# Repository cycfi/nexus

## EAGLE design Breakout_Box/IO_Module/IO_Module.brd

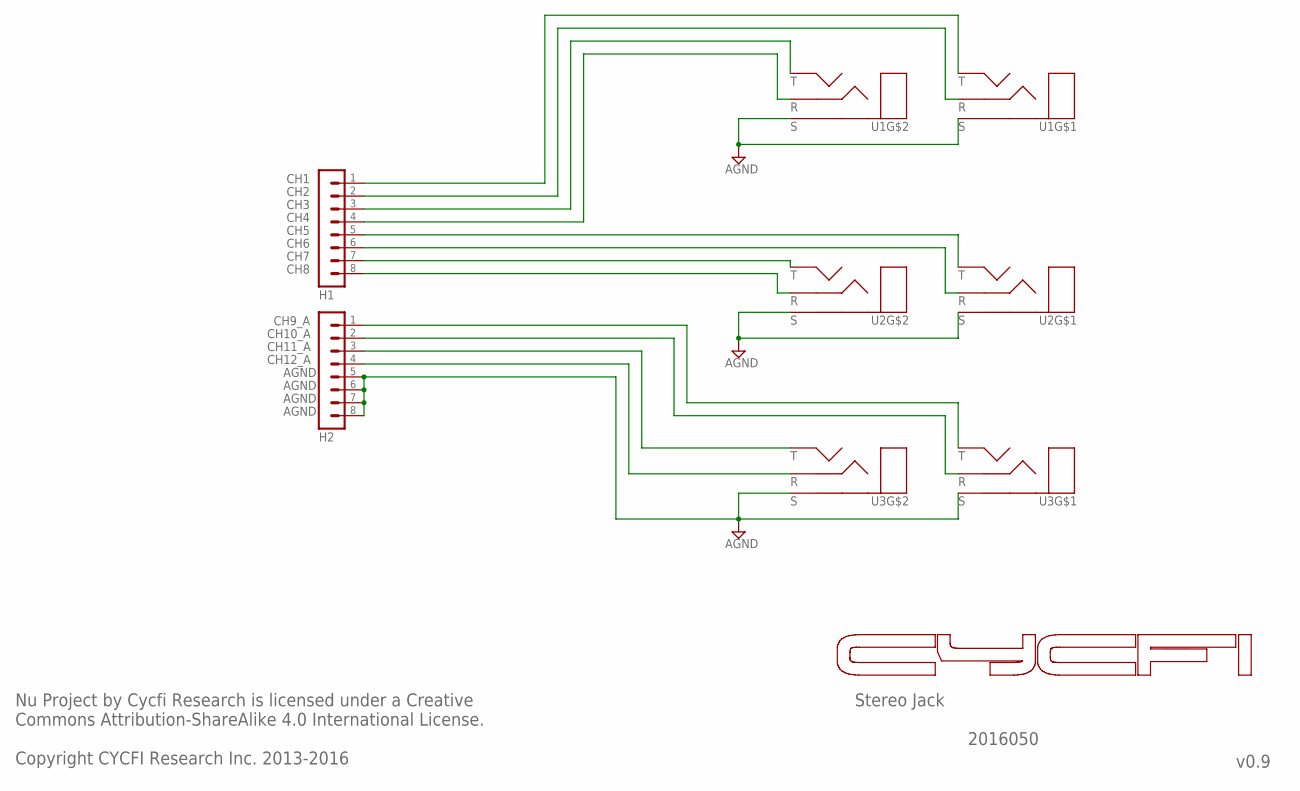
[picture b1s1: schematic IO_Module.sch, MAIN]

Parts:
H1, H2: MA08-1
U1, U2, U3: AGND; NSJ12HC

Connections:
AGND: H2.5, H2.6, H2.7, H2.8, U1.G (DGND), U1.SB (S), U1.ST (S), U2.G (DGND), U2.SB (S), U2.ST (S), U3.G (DGND), U3.SB (S), U3.ST (S)
unnamed: H1.1, U1.TT (T)
unnamed: H1.2, U1.RT (R)
unnamed: H1.3, U1.TB (T)
unnamed: H1.4, U1.RB (R)
unnamed: H1.5, U2.TT (T)
unnamed: H1.6, U2.RT (R)
unnamed: H1.7, U2.TB (T)
unnamed: H1.8, U2.RB (R)
unnamed: H2.1, U3.TT (T)
unnamed: H2.2, U3.RT (R)
unnamed: H2.3, U3.TB (T)
unnamed: H2.4, U3.RB (R)

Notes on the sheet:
Stereo Jack
v0.9
Nu Project by Cycfi Research is licensed under a Creative Commons Attribution-ShareAlike 4.0 International License. Copyright CYCFI Research Inc. 2013-2016
2016050
CH1
CH2
CH3
CH4
CH5
CH6
CH7
CH8
CH9_A
CH10_A
CH11_A
CH12_A

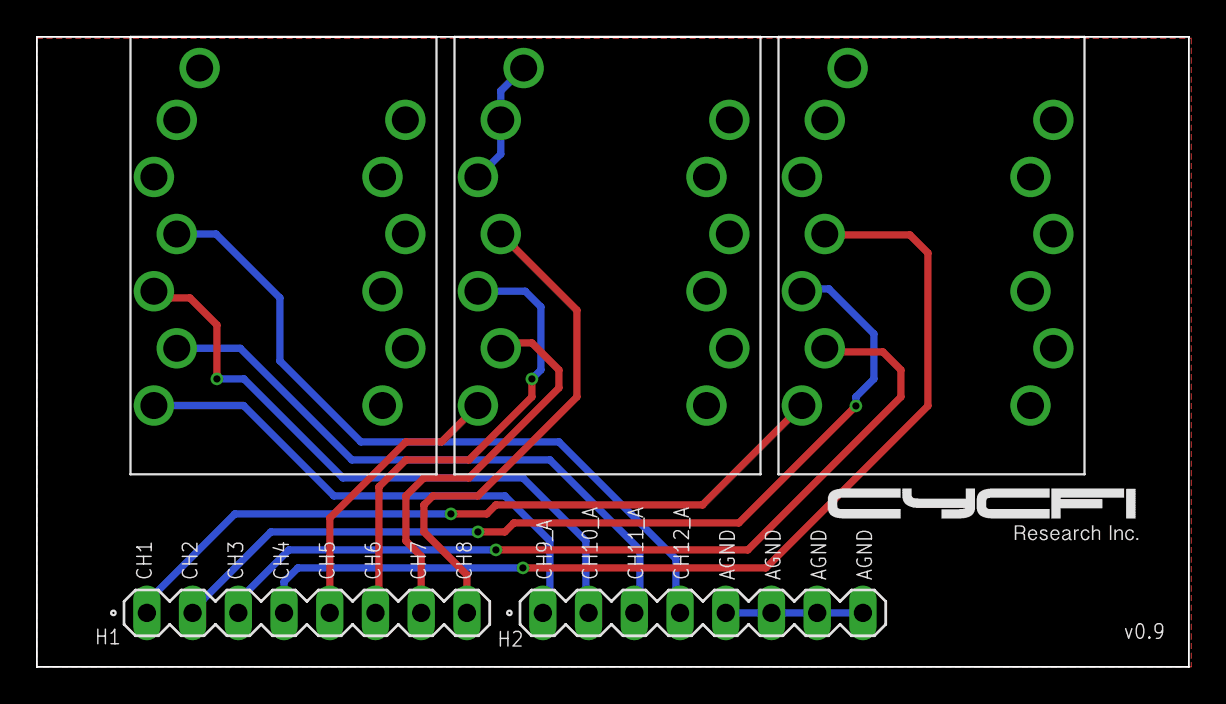
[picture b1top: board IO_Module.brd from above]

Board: 2 copper layers, 64.0 x 35.0 mm, 5 parts (0 on the bottom side), 13 nets.

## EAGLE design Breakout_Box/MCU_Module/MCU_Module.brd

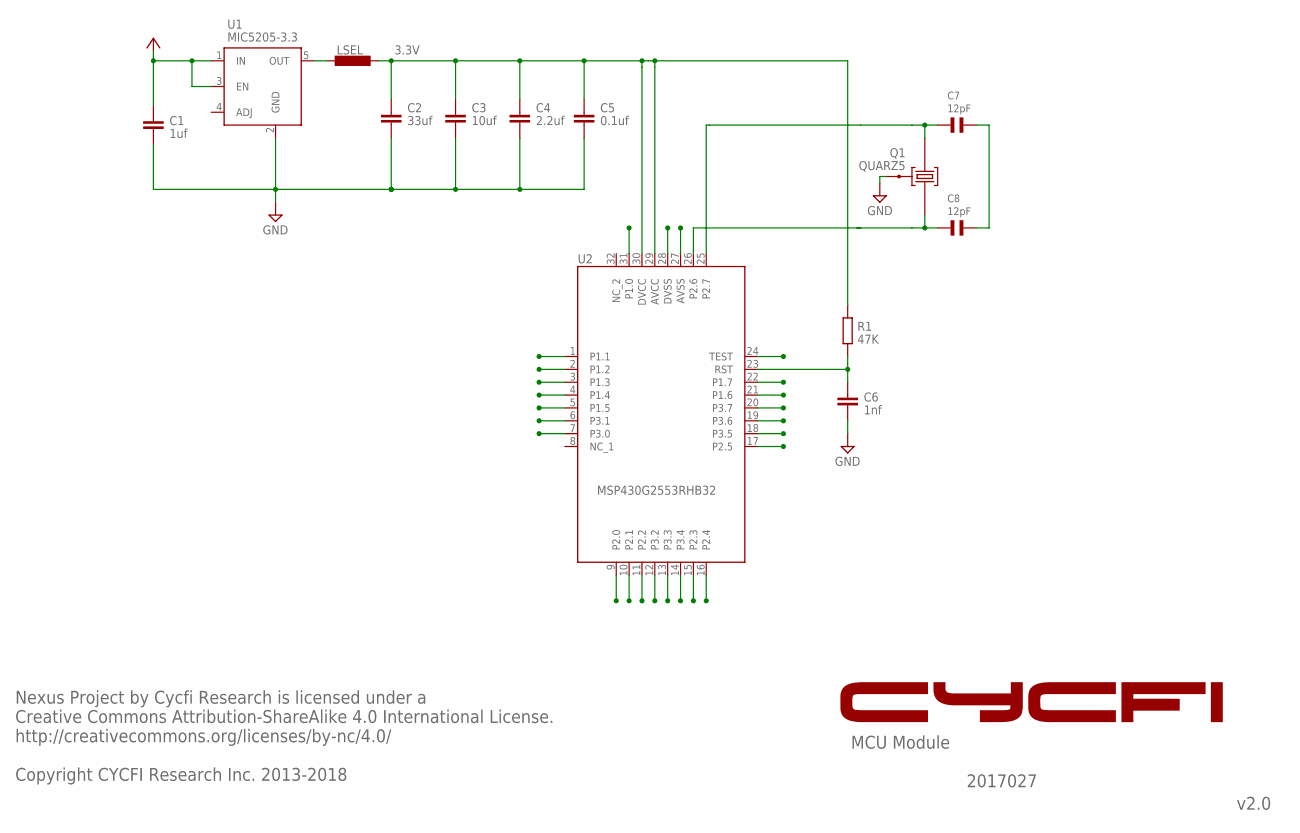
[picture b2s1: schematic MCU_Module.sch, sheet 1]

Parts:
C1: 1uf; C0805
C2: 33uf; C0805
C3: 10uf; C0805
C4: 2.2uf; C0805
C5: 0.1uf; C0603
C6: 1nf; C0603
C7, C8: 12pF; 0603
LSEL: FERRITE_BEAD; 0603
Q1: QUARZ5
R1: 47K; R0402
U1: MIC5205-3.3; SOT23-5
U2: MSP430G2553RHB32; QFN32

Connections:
!RST: C6.1, R1.2, U2.23 (RST); also elsewhere on the board
DVCC(3.3V): C2.1, C3.1, C4.1, C5.1, LSEL.2, R1.1, U2.29 (AVCC), U2.30 (DVCC); also elsewhere on the board
GND: C1.2, C2.2, C3.2, C4.2, C5.2, C6.2, C7.1, C8.1, Q1.GND@0 (0), U1.2 (GND), U2.27 (AVSS), U2.28 (DVSS); also elsewhere on the board
unnamed: LSEL.1, U1.5 (OUT)
NC_2: U2.32 (NC_2)
P1.0: U2.31 (P1.0); also elsewhere on the board
P1.1: U2.1 (P1.1); also elsewhere on the board
P1.2: U2.2 (P1.2); also elsewhere on the board
P1.3: U2.3 (P1.3); also elsewhere on the board
P1.4: U2.4 (P1.4); also elsewhere on the board
P1.5: U2.5 (P1.5); also elsewhere on the board
P1.6: U2.21 (P1.6); also elsewhere on the board
P1.7: U2.22 (P1.7); also elsewhere on the board
P2.0: U2.9 (P2.0); also elsewhere on the board
P2.1: U2.10 (P2.1); also elsewhere on the board
P2.2: U2.11 (P2.2); also elsewhere on the board
P2.3: U2.15 (P2.3); also elsewhere on the board
P2.4: U2.16 (P2.4); also elsewhere on the board
P2.5: U2.17 (P2.5); also elsewhere on the board
P2.6: C8.2, Q1.1, U2.26 (P2.6); also elsewhere on the board
P2.7: C7.2, Q1.2, U2.25 (P2.7); also elsewhere on the board
P3.0: U2.7 (P3.0); also elsewhere on the board
P3.1: U2.6 (P3.1); also elsewhere on the board
P3.2: U2.12 (P3.2); also elsewhere on the board
P3.3: U2.13 (P3.3); also elsewhere on the board
P3.4: U2.14 (P3.4); also elsewhere on the board
P3.5: U2.18 (P3.5); also elsewhere on the board
P3.6: U2.19 (P3.6); also elsewhere on the board
P3.7: U2.20 (P3.7); also elsewhere on the board
TEST: U2.24 (TEST); also elsewhere on the board
VCC: C1.1, U1.1 (IN), U1.3 (EN); also elsewhere on the board

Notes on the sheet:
3.3V
MCU Module
v2.0
Nexus Project by Cycfi Research is licensed under a Creative Commons Attribution-ShareAlike 4.0 International License. http://creativecommons.org/licenses/by-nc/4.0/ Copyright CYCFI Research Inc. 2013-2018
2017027

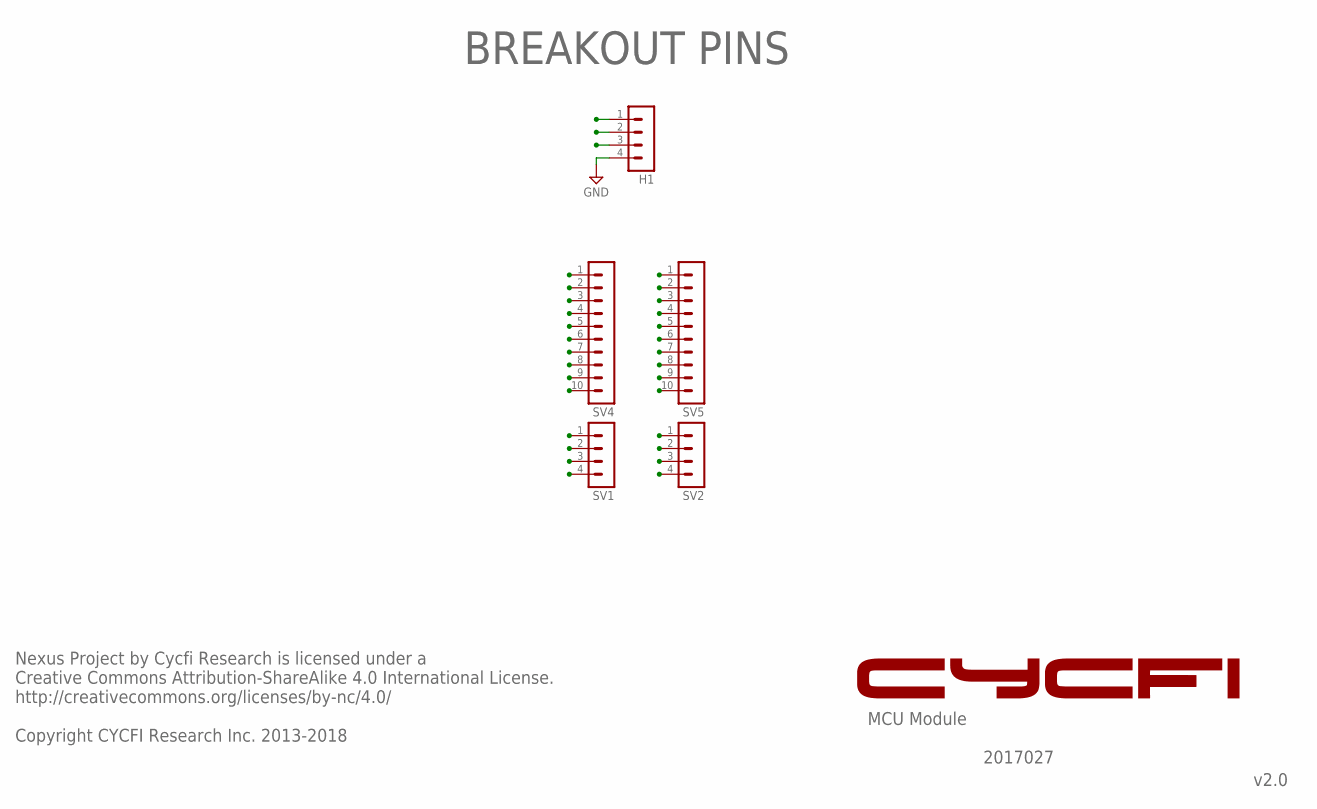
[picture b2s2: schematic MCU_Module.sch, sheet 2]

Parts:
H1: MA04-1
SV1, SV2: MA04-1
SV4, SV5: MA10-1

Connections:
!RST: H1.2; also elsewhere on the board
DVCC(3.3V): H1.3; also elsewhere on the board
GND: H1.4, SV4.1, SV4.2; also elsewhere on the board
P1.0: SV5.3; also elsewhere on the board
P1.1: SV4.3; also elsewhere on the board
P1.2: SV4.4; also elsewhere on the board
P1.3: SV4.5; also elsewhere on the board
P1.4: SV4.6; also elsewhere on the board
P1.5: SV4.7; also elsewhere on the board
P1.6: SV5.7; also elsewhere on the board
P1.7: SV5.6; also elsewhere on the board
P2.0: SV4.10; also elsewhere on the board
P2.1: SV1.1; also elsewhere on the board
P2.2: SV1.2; also elsewhere on the board
P2.3: SV2.3; also elsewhere on the board
P2.4: SV2.2; also elsewhere on the board
P2.5: SV2.1; also elsewhere on the board
P2.6: SV5.4; also elsewhere on the board
P2.7: SV5.5; also elsewhere on the board
P3.0: SV4.9; also elsewhere on the board
P3.1: SV4.8; also elsewhere on the board
P3.2: SV1.3; also elsewhere on the board
P3.3: SV1.4; also elsewhere on the board
P3.4: SV2.4; also elsewhere on the board
P3.5: SV5.10; also elsewhere on the board
P3.6: SV5.9; also elsewhere on the board
P3.7: SV5.8; also elsewhere on the board
TEST: H1.1; also elsewhere on the board
VCC: SV5.1, SV5.2; also elsewhere on the board

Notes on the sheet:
Nexus Project by Cycfi Research is licensed under a Creative Commons Attribution-ShareAlike 4.0 International License. http://creativecommons.org/licenses/by-nc/4.0/ Copyright CYCFI Research Inc. 2013-2018
MCU Module
v2.0
2017027
BREAKOUT PINS

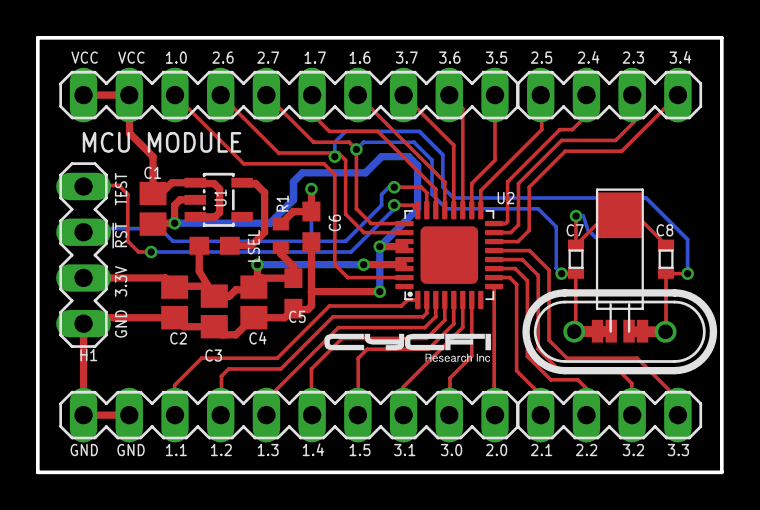
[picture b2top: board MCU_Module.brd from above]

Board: 2 copper layers, 38.0 x 24.1 mm, 18 parts (0 on the bottom side), 30 nets.

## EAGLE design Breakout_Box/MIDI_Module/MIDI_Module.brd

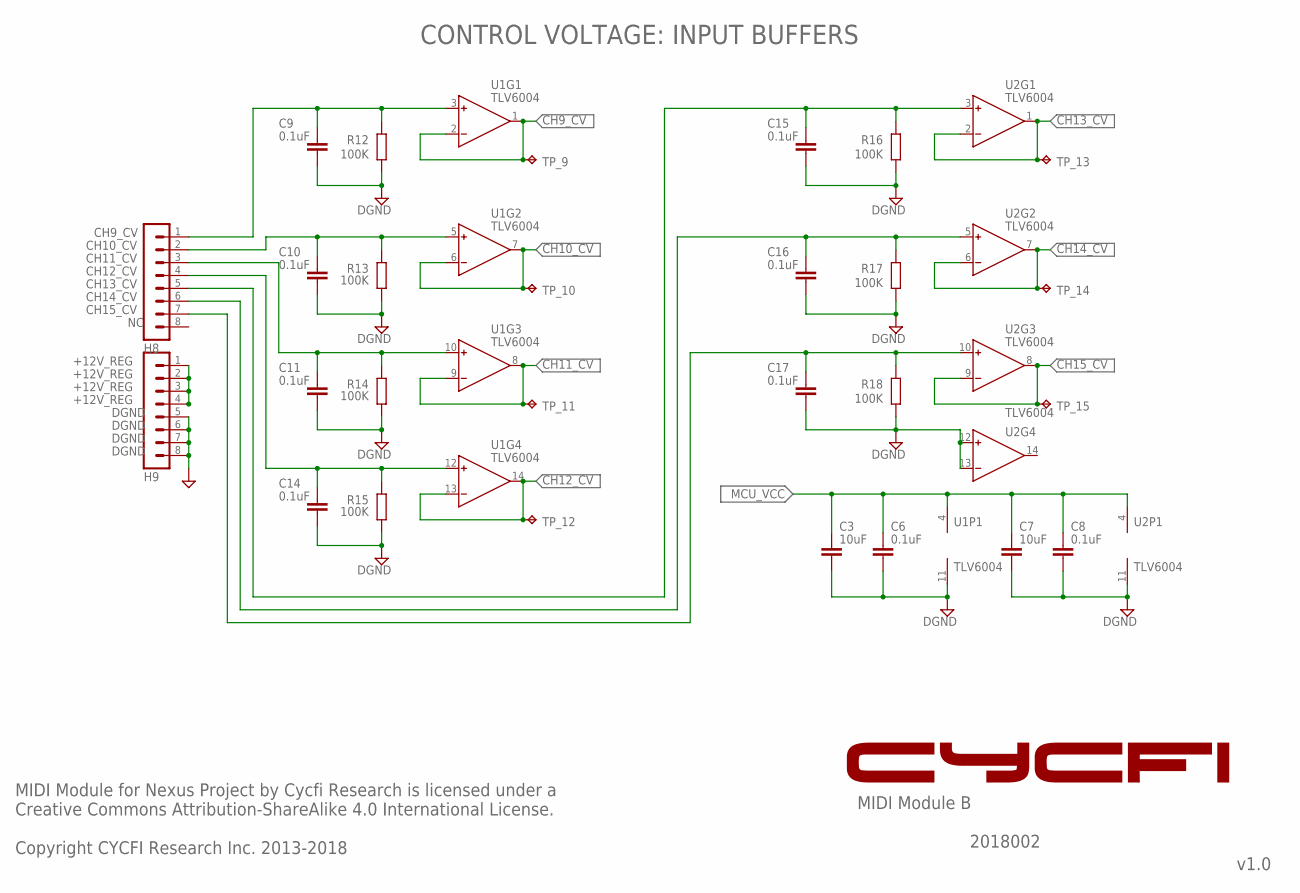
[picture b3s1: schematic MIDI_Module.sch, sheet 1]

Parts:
C3, C7: 10uF; C0805
C6, C8, C9, C10, C11, C14, C15, C16, C17: 0.1uF; C0603
H8, H9: MA08-1
R12, R13, R14, R15, R16, R17, R18: 100K; R0402
TP_9, TP_10, TP_11, TP_12, TP_13, TP_14, TP_15: TPB1,27; B1,27
U1, U2: TLV6004; SSOP-14

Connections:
+12V_REG: H9.1, H9.2, H9.3, H9.4; also elsewhere on the board
CH9_CV: TP_9.TP, U1.1 (OUT), U1.2 (IN-); also elsewhere on the board
CH10_CV: TP_10.TP, U1.6 (IN-), U1.7 (OUT); also elsewhere on the board
CH11_CV: TP_11.TP, U1.8 (OUT), U1.9 (IN-); also elsewhere on the board
CH12_CV: TP_12.TP, U1.13 (IN-), U1.14 (OUT); also elsewhere on the board
CH13_CV: TP_13.TP, U2.1 (OUT), U2.2 (IN-); also elsewhere on the board
CH14_CV: TP_14.TP, U2.6 (IN-), U2.7 (OUT); also elsewhere on the board
CH15_CV: TP_15.TP, U2.8 (OUT), U2.9 (IN-); also elsewhere on the board
DGND: C3.2, C6.2, C7.2, C8.2, C9.2, C10.2, C11.2, C14.2, C15.2, C16.2, C17.2, H9.5, H9.6, H9.7, H9.8, R12.1, R13.1, R14.1, R15.1, R16.1, R17.1, R18.1, U1.11 (V-), U2.11 (V-), U2.12 (IN+), U2.13 (IN-); also elsewhere on the board
MCU_VCC: C3.1, C6.1, C7.1, C8.1, U1.4 (V+), U2.4 (V+); also elsewhere on the board
unnamed: C9.1, H8.1, R12.2, U1.3 (IN+)
unnamed: C10.1, H8.2, R13.2, U1.5 (IN+)
unnamed: C11.1, H8.3, R14.2, U1.10 (IN+)
unnamed: C14.1, H8.4, R15.2, U1.12 (IN+)
unnamed: C15.1, H8.5, R16.2, U2.3 (IN+)
unnamed: C16.1, H8.6, R17.2, U2.5 (IN+)
unnamed: C17.1, H8.7, R18.2, U2.10 (IN+)

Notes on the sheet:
MIDI Module B
v1.0
2018002
CH9_CV
CH10_CV
CH11_CV
CH12_CV
CH13_CV
CH14_CV
CH15_CV
DGND
CONTROL VOLTAGE: INPUT BUFFERS
MIDI Module for Nexus Project by Cycfi Research is licensed under a Creative Commons Attribution-ShareAlike 4.0 International License. Copyright CYCFI Research Inc. 2013-2018

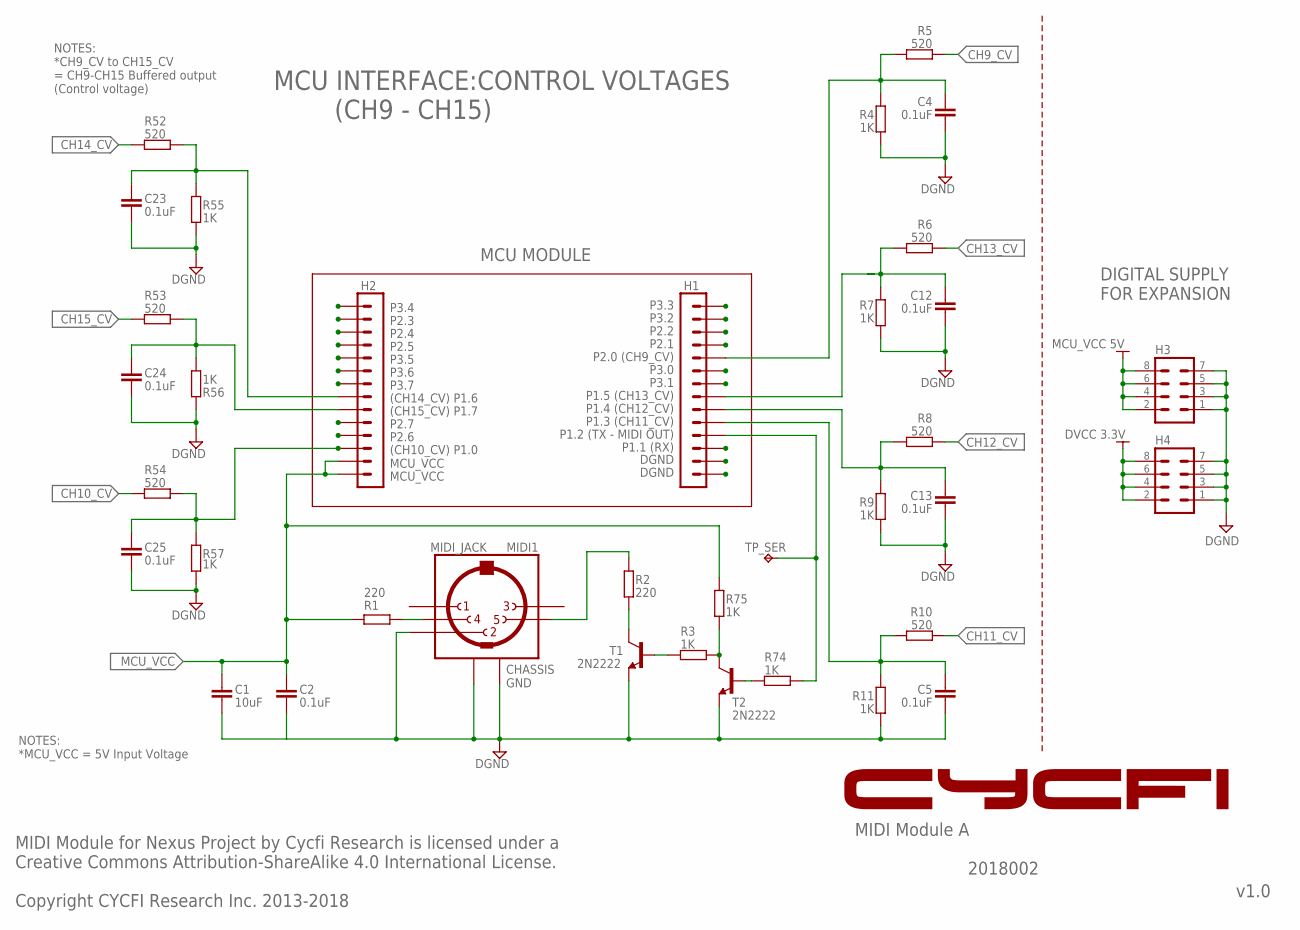
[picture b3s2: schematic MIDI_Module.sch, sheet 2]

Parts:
C1: 10uF; C0805
C2, C4, C5, C12, C13, C23, C24, C25: 0.1uF; C0603
H1, H2: 14PIN-TH-2.54MM; 14P-TH-2.54MM
H3, H4: MA04-2
MIDI1: MIDI_JACK
R1, R2: 220; R0402
R3, R4, R7, R9, R11, R55, R56, R57, R74, R75: 1K; R0402
R5, R6, R8, R10, R52, R53, R54: 520; R0402
T1, T2: 2N2222; SOT23-3
TP_SER: TPB1,27; B1,27

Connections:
CH9D: C4.1, H1.10, R4.1, R5.2
CH9_CV: R5.1; also elsewhere on the board
CH10A: C25.1, H2.12, R54.2, R57.1
CH10_CV: R54.1; also elsewhere on the board
CH11A: C5.1, H1.5, R10.2, R11.1
CH11_CV: R10.1; also elsewhere on the board
CH12A: C13.1, H1.6, R8.2, R9.1
CH12_CV: R8.1; also elsewhere on the board
CH13A: C12.1, H1.7, R6.2, R7.1
CH13_CV: R6.1; also elsewhere on the board
CH14A: C23.1, H2.8, R52.2, R55.1
CH14_CV: R52.1; also elsewhere on the board
CH15A: C24.1, H2.9, R53.2, R56.1
CH15_CV: R53.1; also elsewhere on the board
DGND: C1.2, C2.2, C4.2, C5.2, C12.2, C13.2, C23.2, C24.2, C25.2, H1.1, H1.2, H3.1, H3.3, H3.5, H3.7, H4.1, H4.3, H4.5, H4.7, MIDI1.2, MIDI1.G1, MIDI1.G2, R4.2, R7.2, R9.2, R11.2, R55.2, R56.2, R57.2, T1.2 (E), T2.2 (E); also elsewhere on the board
DVCC: H4.2, H4.4, H4.6, H4.8; also elsewhere on the board
MCU_VCC: C1.1, C2.1, H2.13, H2.14, H3.2, H3.4, H3.6, H3.8, R1.2, R75.2; also elsewhere on the board
MIDI_OUT: H1.4, R74.1, TP_SER.TP
unnamed: MIDI1.5, R2.2
unnamed: R2.1, T1.3 (C)
unnamed: R3.2, T1.1 (B)
unnamed: MIDI1.4, R1.1
unnamed: R74.2, T2.1 (B)
unnamed: R3.1, R75.1, T2.3 (C)
P1.1: H1.3
P2.1: H1.11
P2.2: H1.12
P2.3: H2.2
P2.4: H2.3
P2.5: H2.4
P2.6: H2.11
P2.7: H2.10
P3.1: H1.8
P3.2: H1.13
P3.3: H1.14
P3.4: H2.1
P3.5: H2.5
P3.6: H2.6
P3.7: H2.7

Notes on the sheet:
MIDI Module A
v1.0
2018002
P3.3
P3.2
P2.2
P2.1
P2.0 (CH9_CV)
P3.0
P3.1
P1.5 (CH13_CV)
P1.4 (CH12_CV)
P1.3 (CH11_CV)
P1.2 (TX - MIDI OUT)
P1.1 (RX)
P3.4
P2.3
P2.4
P2.5
P3.5
P3.6
P3.7
(CH14_CV) P1.6
(CH15_CV) P1.7
P2.7
P2.6
(CH10_CV) P1.0
MCU MODULE
NOTES: *CH9_CV to CH15_CV = CH9-CH15 Buffered output (Control voltage)
CHASSIS GND
NOTES: *MCU_VCC = 5V Input Voltage
MCU INTERFACE:CONTROL VOLTAGES (CH9 - CH15)
DIGITAL SUPPLY FOR EXPANSION
MCU_VCC 5V
DVCC 3.3V
MIDI Module for Nexus Project by Cycfi Research is licensed under a Creative Commons Attribution-ShareAlike 4.0 International License. Copyright CYCFI Research Inc. 2013-2018

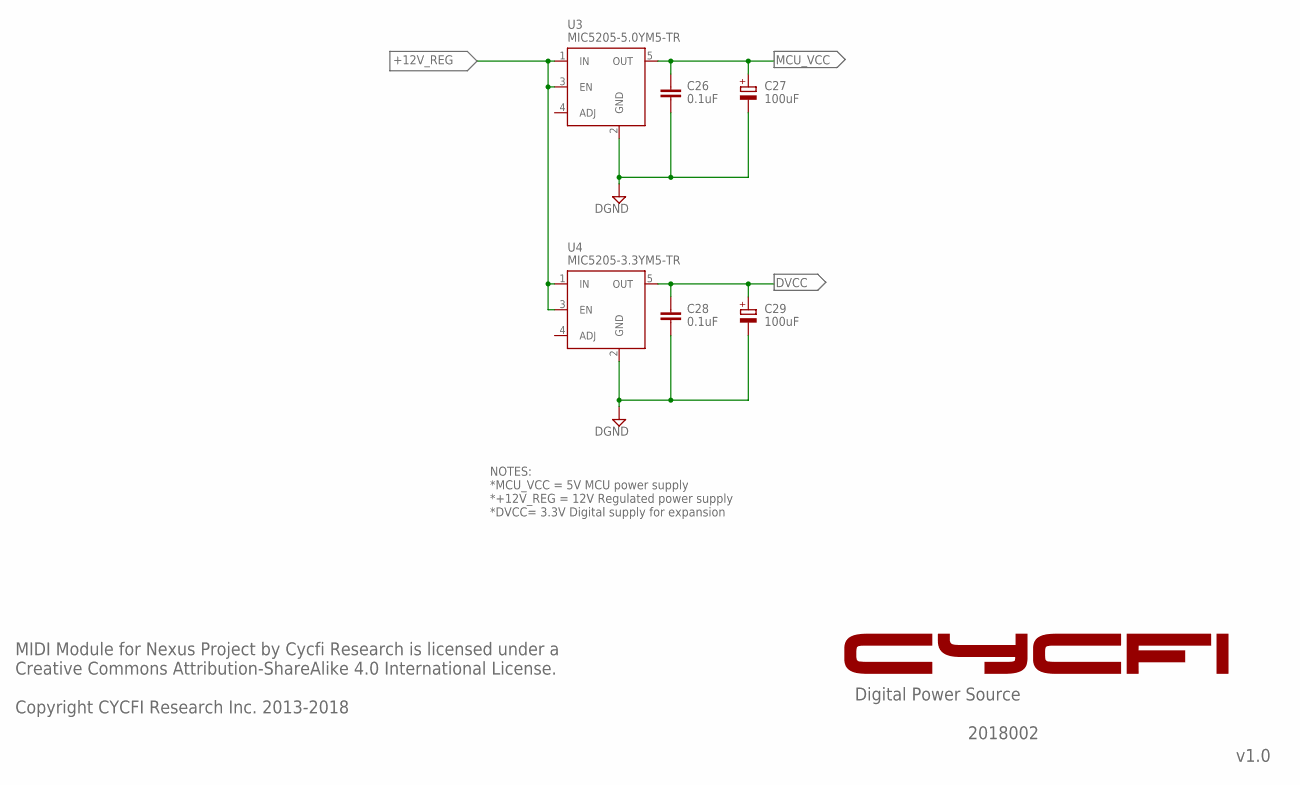
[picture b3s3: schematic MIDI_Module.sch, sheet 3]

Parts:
C26, C28: 0.1uF; C0603
C27, C29: 100uF; 153CLV-0505
U3: MIC5205-5.0YM5-TR; SOT23-5
U4: MIC5205-3.3YM5-TR; SOT23-5

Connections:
+12V_REG: U3.1 (IN), U3.3 (EN), U4.1 (IN), U4.3 (EN); also elsewhere on the board
DGND: C26.2, C27.-, C28.2, C29.-, U3.2 (GND), U4.2 (GND); also elsewhere on the board
DVCC: C28.1, C29.+, U4.5 (OUT); also elsewhere on the board
MCU_VCC: C26.1, C27.+, U3.5 (OUT); also elsewhere on the board

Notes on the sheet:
Digital Power Source
NOTES: *MCU_VCC = 5V MCU power supply *+12V_REG = 12V Regulated power supply *DVCC= 3.3V Digital supply for expansion
v1.0
2018002
MIDI Module for Nexus Project by Cycfi Research is licensed under a Creative Commons Attribution-ShareAlike 4.0 International License. Copyright CYCFI Research Inc. 2013-2018

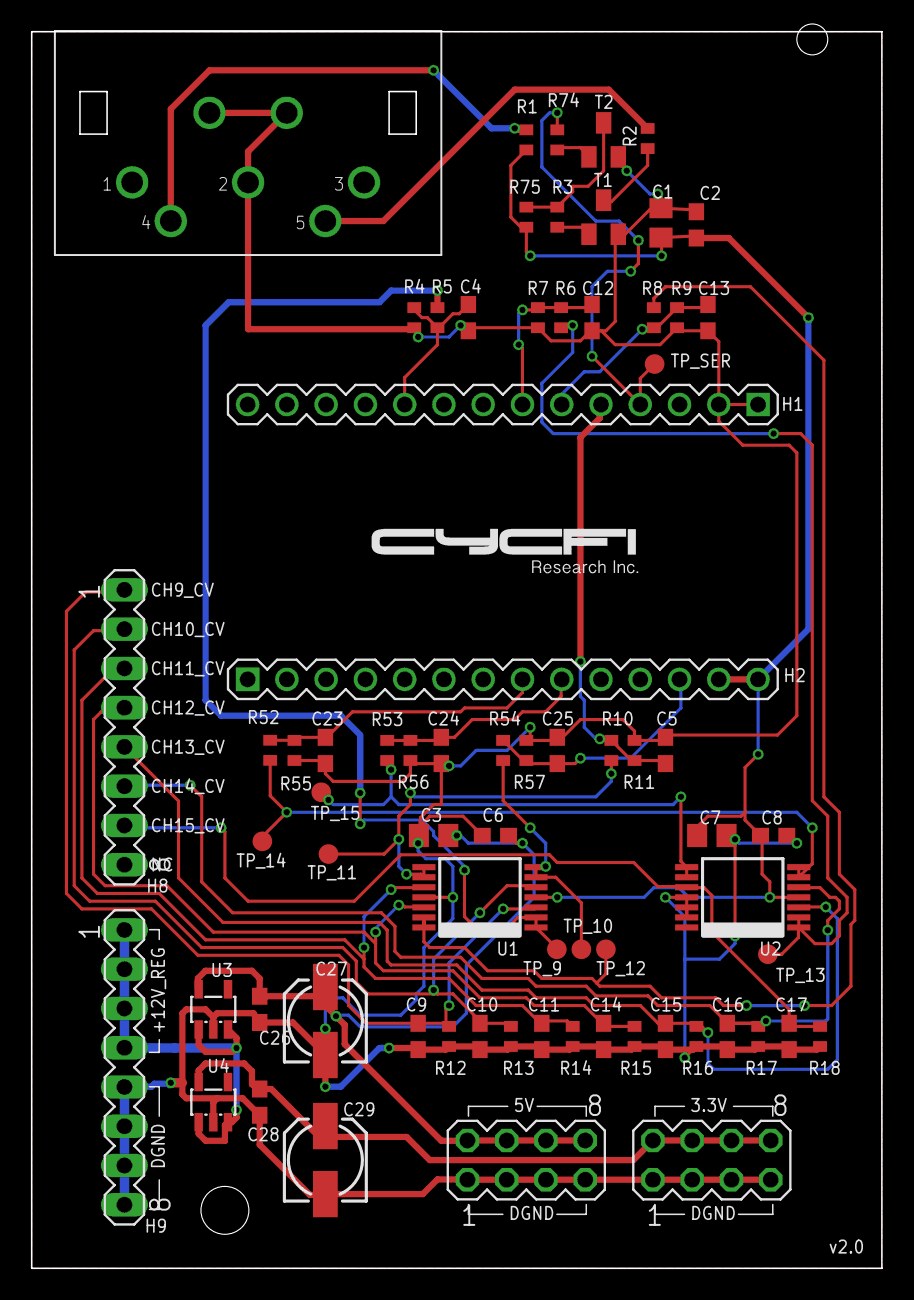
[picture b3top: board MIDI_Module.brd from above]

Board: 2 copper layers, 55.0 x 80.0 mm, 71 parts (0 on the bottom side), 32 nets.

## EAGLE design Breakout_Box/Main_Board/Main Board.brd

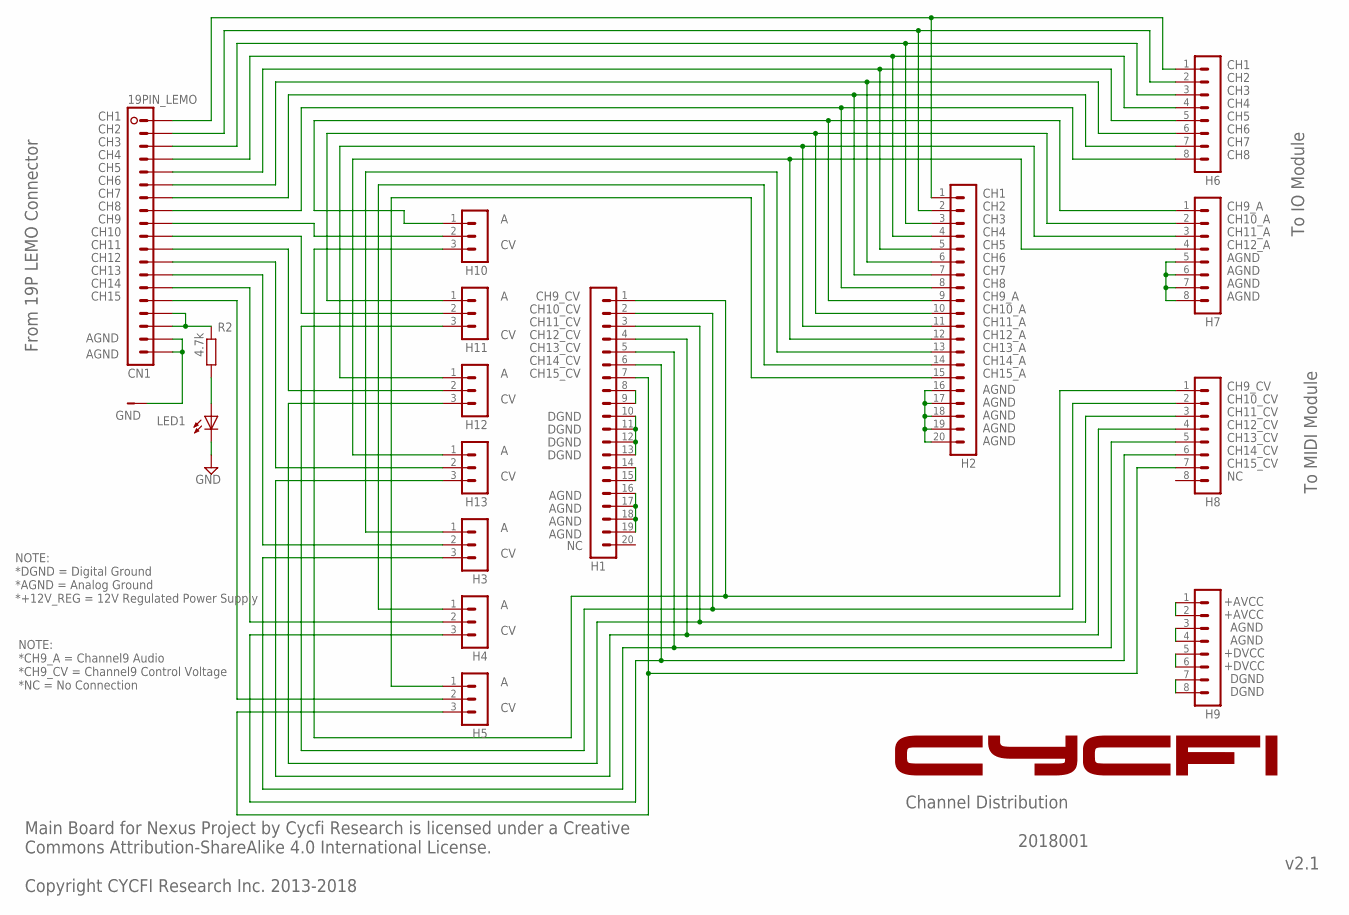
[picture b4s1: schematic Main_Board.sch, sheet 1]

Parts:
CN1: 19PIN_LEMO
GND: TH-PAD-1.6/0.8
H1, H2: MA20-1
H3, H4, H5, H10, H11, H12, H13: MA03-1_EDITED; MA03-1_
H6, H7, H8, H9: MA08-1
LED1: LED3MM
R2: 4.7k; R0402

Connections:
+AVCC: CN1.P$16 (16), CN1.P$17 (17), H1.14, H1.15, H9.1, H9.2, R2.1; also elsewhere on the board
+DVCC: H1.8, H1.9, H9.5, H9.6; also elsewhere on the board
GND: CN1.P$18 (18), CN1.P$19 (19), GND.1, H1.10, H1.11, H1.12, H1.13, H1.16, H1.17, H1.18, H1.19, H2.16, H2.17, H2.18, H2.19, H2.20, H7.5, H7.6, H7.7, H7.8, H9.3, H9.4, H9.7, H9.8, LED1.K (C); also elsewhere on the board
unnamed: H2.13, H3.1
unnamed: H2.14, H4.1
unnamed: CN1.P$1 (1), H2.1, H6.1
unnamed: CN1.P$2 (2), H2.2, H6.2
unnamed: CN1.P$3 (3), H2.3, H6.3
unnamed: CN1.P$4 (4), H2.4, H6.4
unnamed: CN1.P$5 (5), H2.5, H6.5
unnamed: H1.1, H8.1, H10.3
unnamed: CN1.P$6 (6), H2.6, H6.6
unnamed: CN1.P$7 (7), H2.7, H6.7
unnamed: CN1.P$8 (8), H2.8, H6.8
unnamed: CN1.P$9 (9), H10.2
unnamed: CN1.P$10 (10), H11.2
unnamed: CN1.P$11 (11), H12.2
unnamed: CN1.P$12 (12), H13.2
unnamed: H2.15, H5.1
unnamed: H2.10, H7.2, H11.1
unnamed: LED1.A, R2.2
unnamed: H1.3, H8.3, H12.3
unnamed: H1.2, H8.2, H11.3
unnamed: H2.12, H7.4, H13.1
unnamed: H2.11, H7.3, H12.1
unnamed: H1.4, H8.4, H13.3
unnamed: H2.9, H7.1, H10.1
unnamed: H1.5, H3.3, H8.5
unnamed: H1.6, H4.3, H8.6
unnamed: H1.7, H5.3, H8.7
unnamed: CN1.P$13 (13), H3.2
unnamed: CN1.P$14 (14), H4.2
unnamed: CN1.P$15 (15), H5.2

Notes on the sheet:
Channel Distribution
v2.1
2018001
CH1
CH2
CH3
CH4
CH5
CH6
CH7
CH8
CH9_A
CH10_A
CH11_A
CH12_A
CH9_CV
CH10_CV
CH11_CV
CH12_CV
CH13_CV
CH14_CV
CH15_CV
AGND
From 19P LEMO Connector
To IO Module
To MIDI Module
NOTE: *DGND = Digital Ground *AGND = Analog Ground *+12V_REG = 12V Regulated Power Supply
NOTE: *CH9_A = Channel9 Audio *CH9_CV = Channel9 Control Voltage *NC = No Connection
Main Board for Nexus Project by Cycfi Research is licensed under a Creative Commons Attribution-ShareAlike 4.0 International License. Copyright CYCFI Research Inc. 2013-2018
CH9
CH10
CH11
CH12
CH13
CH14
CH15
CH13_A
CH14_A
CH15_A
DGND

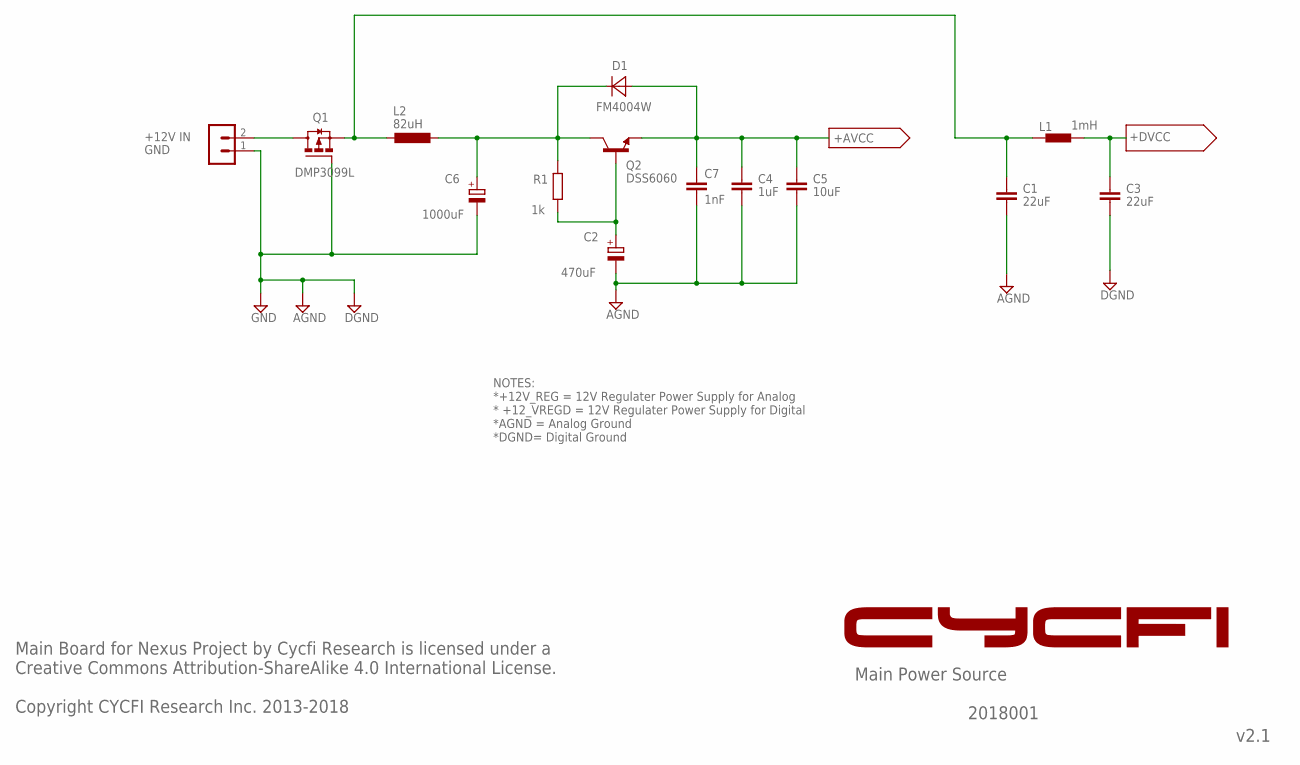
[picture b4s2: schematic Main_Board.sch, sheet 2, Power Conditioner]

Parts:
C1, C3: 22uF; C0805
C2: 470uF; 140CLH-1010
C4: 1uF; C0603
C5: 10uF; C0603
C6: 1000uF; 140CLH-1010
C7: 1nF; C0402K
D1: FM4004W; SMX
H14: MA02-1
L1: 1mH; SDR
L2: 82uH; L1280
Q1: DMP3099L; SOT23
Q2: DSS6060; SOT-223-4
R1: 1k; R0402

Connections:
+AVCC: C4.1, C5.1, C7.1, D1.ANODE (A), Q2.P$3 (E); also elsewhere on the board
+DVCC: C3.1, L1.P$2 (2); also elsewhere on the board
GND: C1.2, C2.-, C3.2, C4.2, C5.2, C6.-, C7.2, H14.1, Q1.1 (G); also elsewhere on the board
unnamed: H14.2, Q1.3 (D)
unnamed: C1.1, L1.P$1 (1), L2.P$1 (1), Q1.2 (S)
unnamed: C2.+, Q2.P$1 (B), R1.1
unnamed: C6.+, D1.CATHODE (C), L2.P$2 (2), Q2.P$2 (C), Q2.P$4 (C), R1.2

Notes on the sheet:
Main Power Source
NOTES: *+12V_REG = 12V Regulater Power Supply for Analog * +12_VREGD = 12V Regulater Power Supply for Digital *AGND = Analog Ground *DGND= Digital Ground
v2.1
+12V IN
GND
Main Board for Nexus Project by Cycfi Research is licensed under a Creative Commons Attribution-ShareAlike 4.0 International License. Copyright CYCFI Research Inc. 2013-2018
2018001

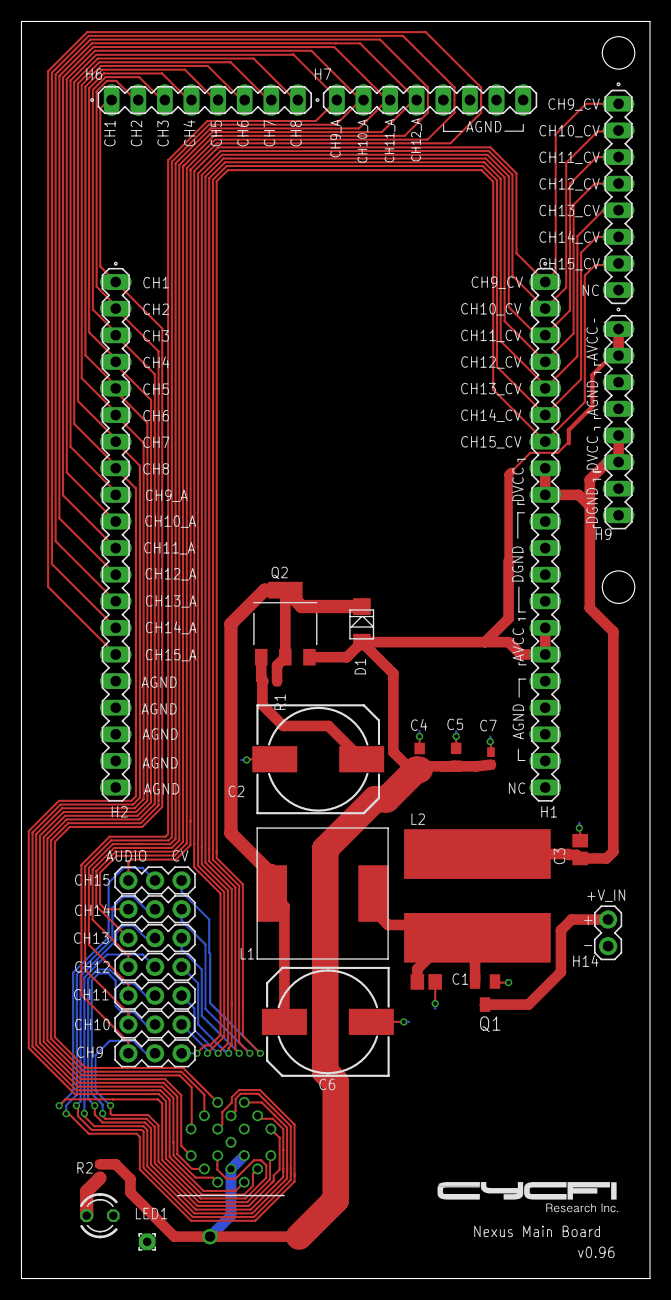
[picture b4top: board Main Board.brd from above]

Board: 2 copper layers, 60.0 x 120.0 mm, 31 parts (0 on the bottom side), 37 nets.

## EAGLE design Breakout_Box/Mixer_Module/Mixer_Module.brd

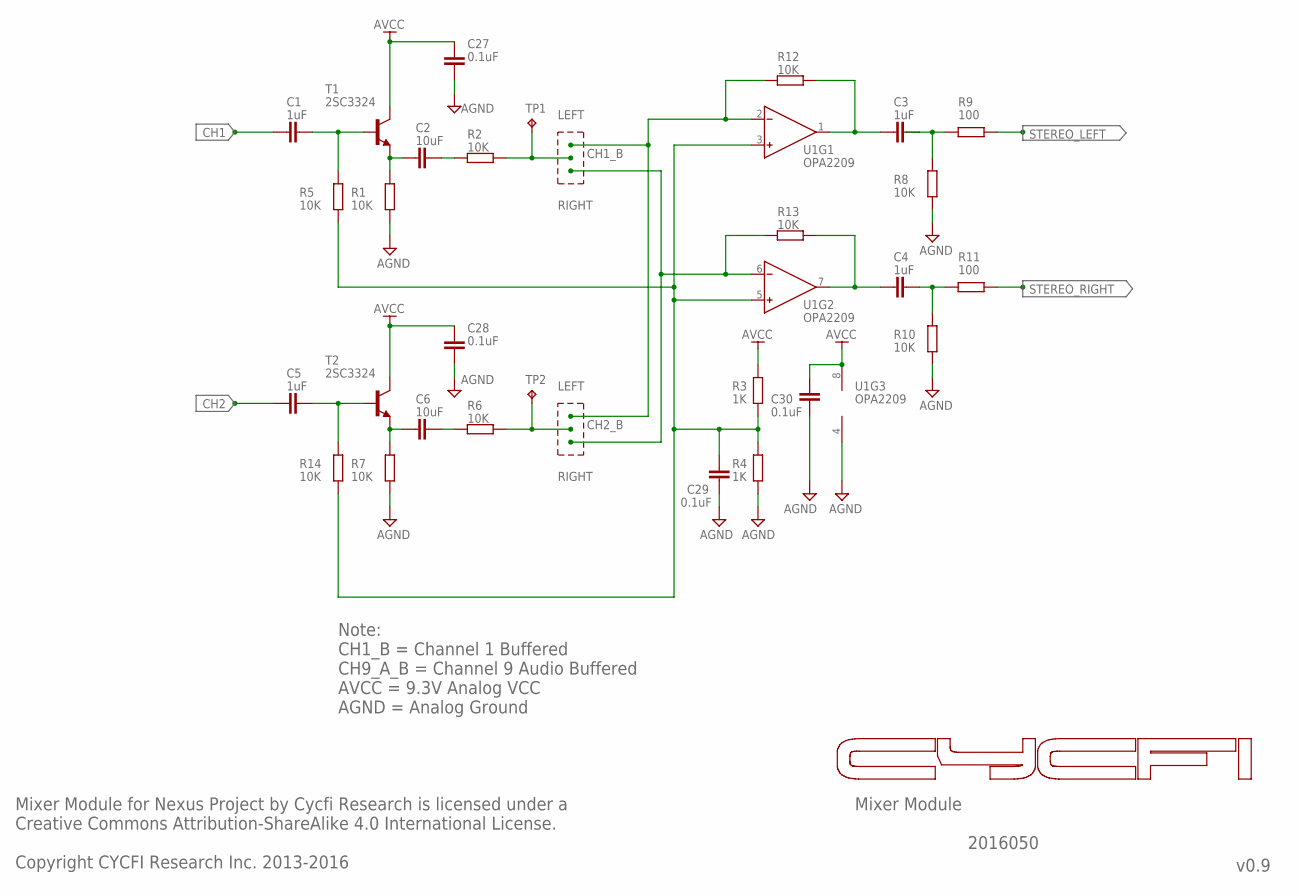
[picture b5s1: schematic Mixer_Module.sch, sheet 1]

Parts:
C1, C3, C4, C5: 1uF; C0603
C2, C6: 10uF; C0603
C27, C28, C29, C30: 0.1uF; C0603
R1, R2, R5, R6, R7, R8, R10, R12, R13, R14: 10K; R0402
R3, R4: 1K; R0402
R9, R11: 100; R0402
T1, T2: 2SC3324; SOT23
TP1, TP2: TPB1,27; B1,27
U1: OPA2209; MSOP8

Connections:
AGND: C27.1, C28.1, C29.1, C30.1, R1.2, R4.1, R7.2, R8.1, R10.1, U1.4 (V-); also elsewhere on the board
AVCC: C27.2, C28.2, C30.2, R3.2, T1.3 (C), T2.3 (C), U1.8 (V+); also elsewhere on the board
CH1: C1.1; also elsewhere on the board
CH1_B: R2.2, TP1.TP; also elsewhere on the board
CH2: C5.1; also elsewhere on the board
CH2_B: R6.2, TP2.TP; also elsewhere on the board
LEFT: R12.1, U1.2 (IN-); also elsewhere on the board
unnamed: C6.1, R7.1, T2.2 (E)
unnamed: C2.1, R1.1, T1.2 (E)
unnamed: C1.2, R5.1, T1.1 (B)
unnamed: C3.2, R8.2, R9.2
unnamed: C3.1, R12.2, U1.1 (OUT)
unnamed: C4.1, R13.2, U1.7 (OUT)
unnamed: C2.2, R2.1
unnamed: C4.2, R10.2, R11.2
unnamed: C6.2, R6.1
unnamed: C5.2, R14.1, T2.1 (B)
unnamed: C29.2, R3.1, R4.2, R5.2, R14.2, U1.3 (IN+), U1.5 (IN+)
RIGHT: R13.1, U1.6 (IN-); also elsewhere on the board
STEREO_LEFT: R9.1; also elsewhere on the board
STEREO_RIGHT: R11.1; also elsewhere on the board

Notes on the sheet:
Mixer Module
v0.9
Mixer Module for Nexus Project by Cycfi Research is licensed under a Creative Commons Attribution-ShareAlike 4.0 International License. Copyright CYCFI Research Inc. 2013-2016
2016050
Note: CH1_B = Channel 1 Buffered CH9_A_B = Channel 9 Audio Buffered AVCC = 9.3V Analog VCC AGND = Analog Ground
